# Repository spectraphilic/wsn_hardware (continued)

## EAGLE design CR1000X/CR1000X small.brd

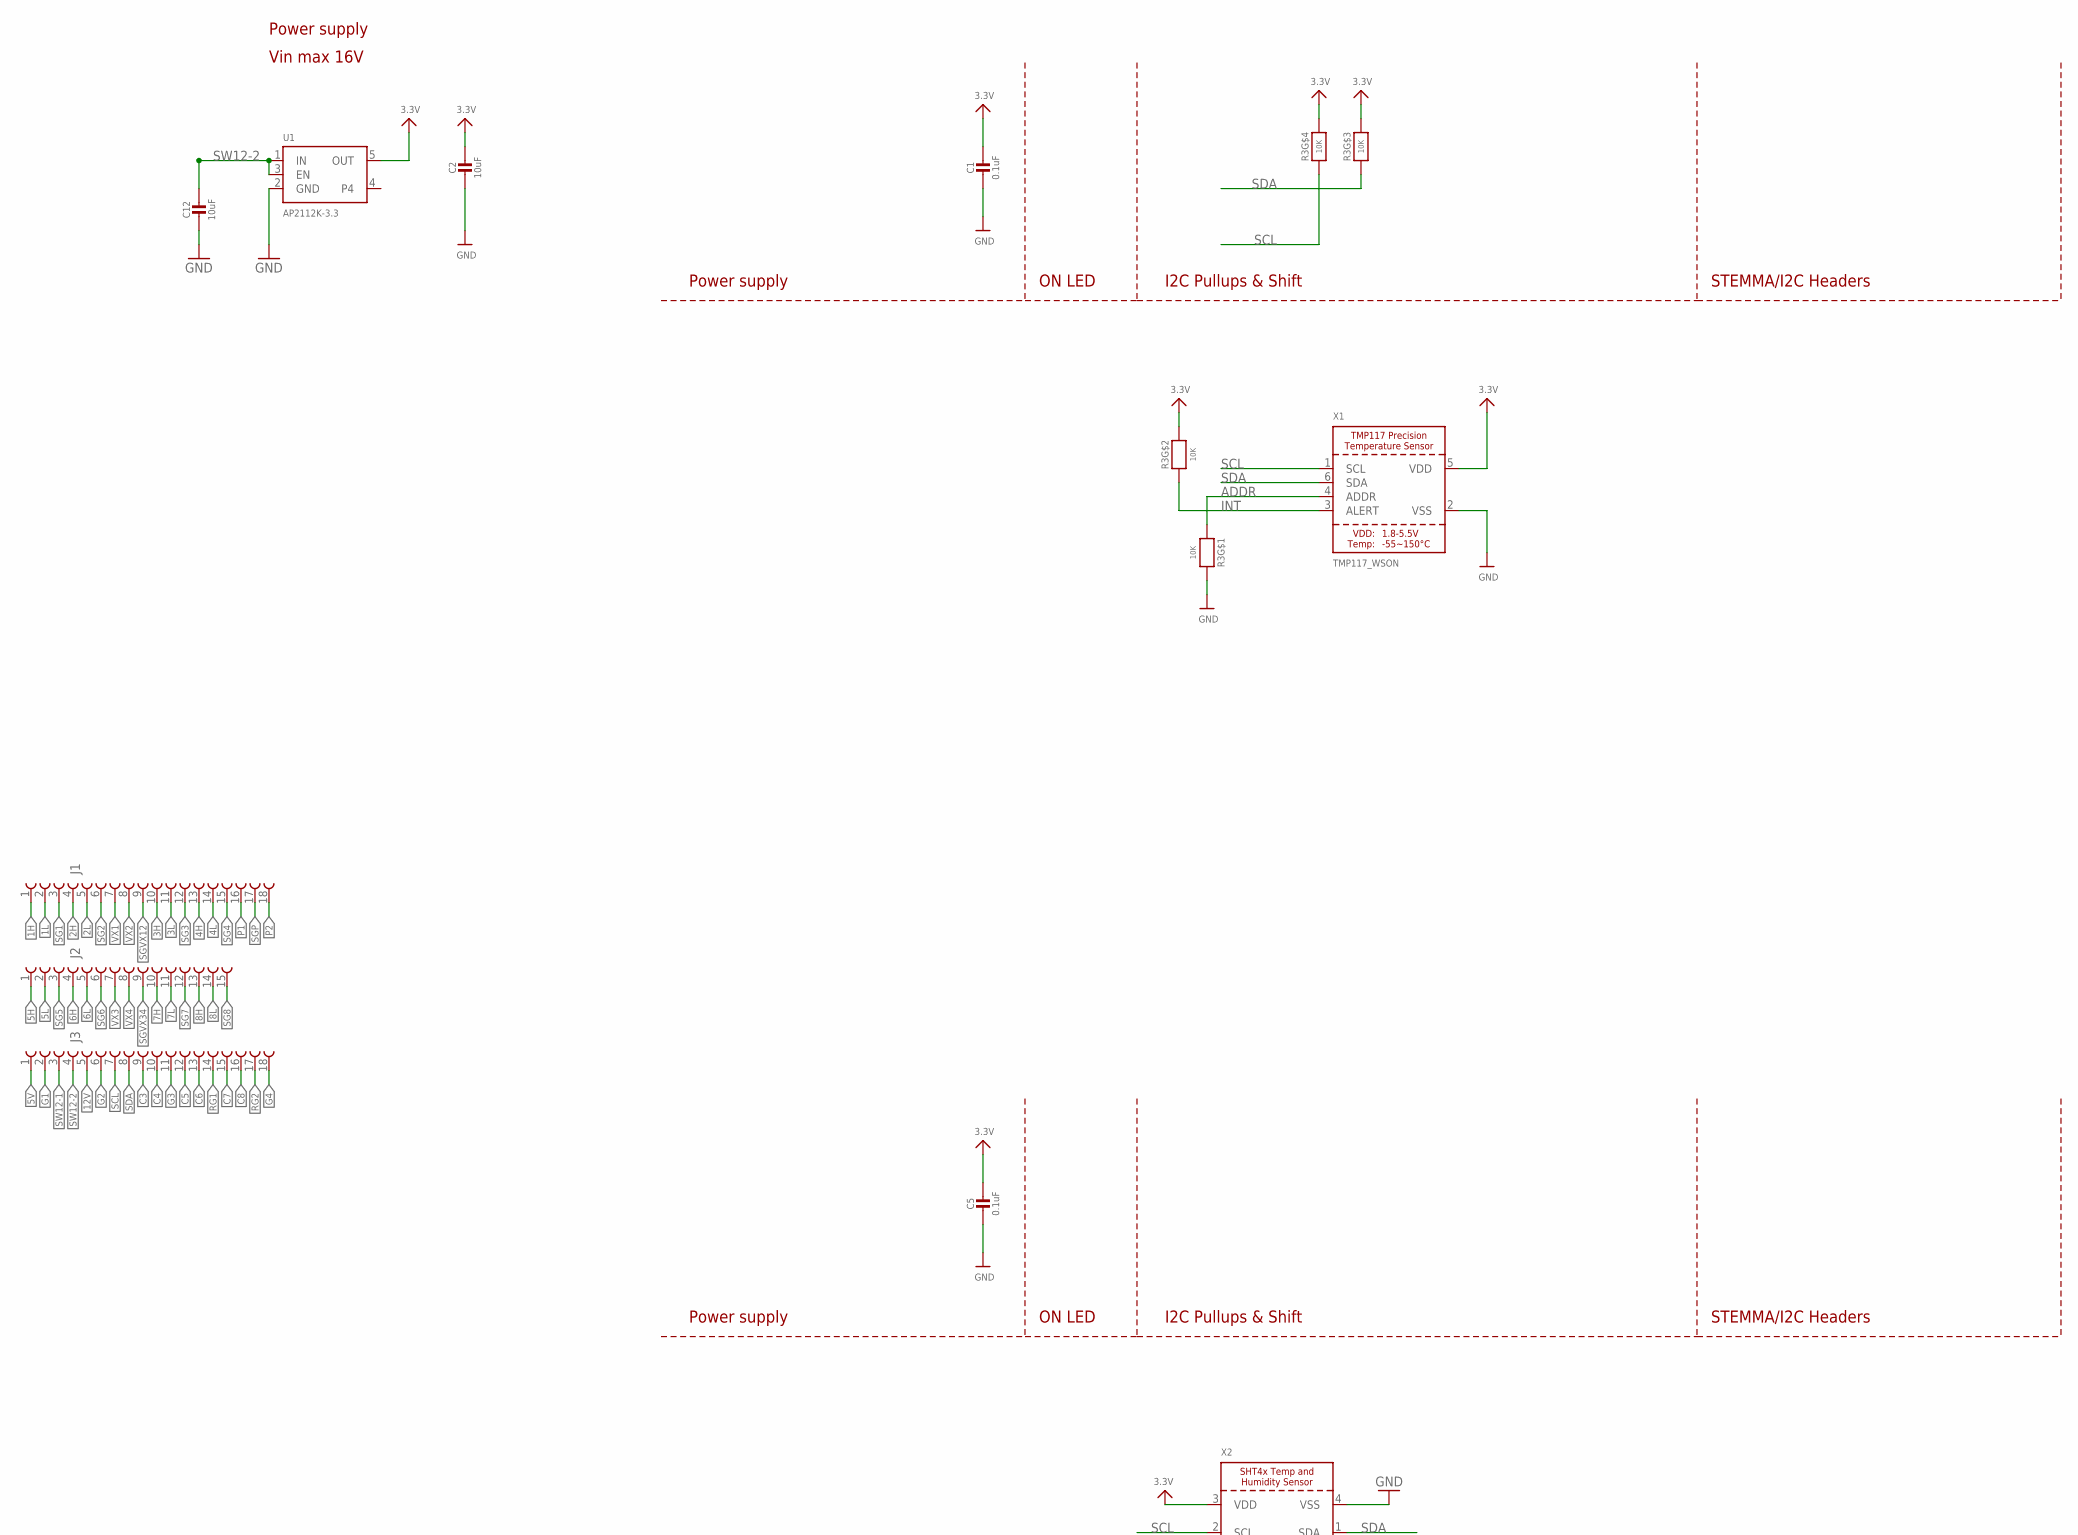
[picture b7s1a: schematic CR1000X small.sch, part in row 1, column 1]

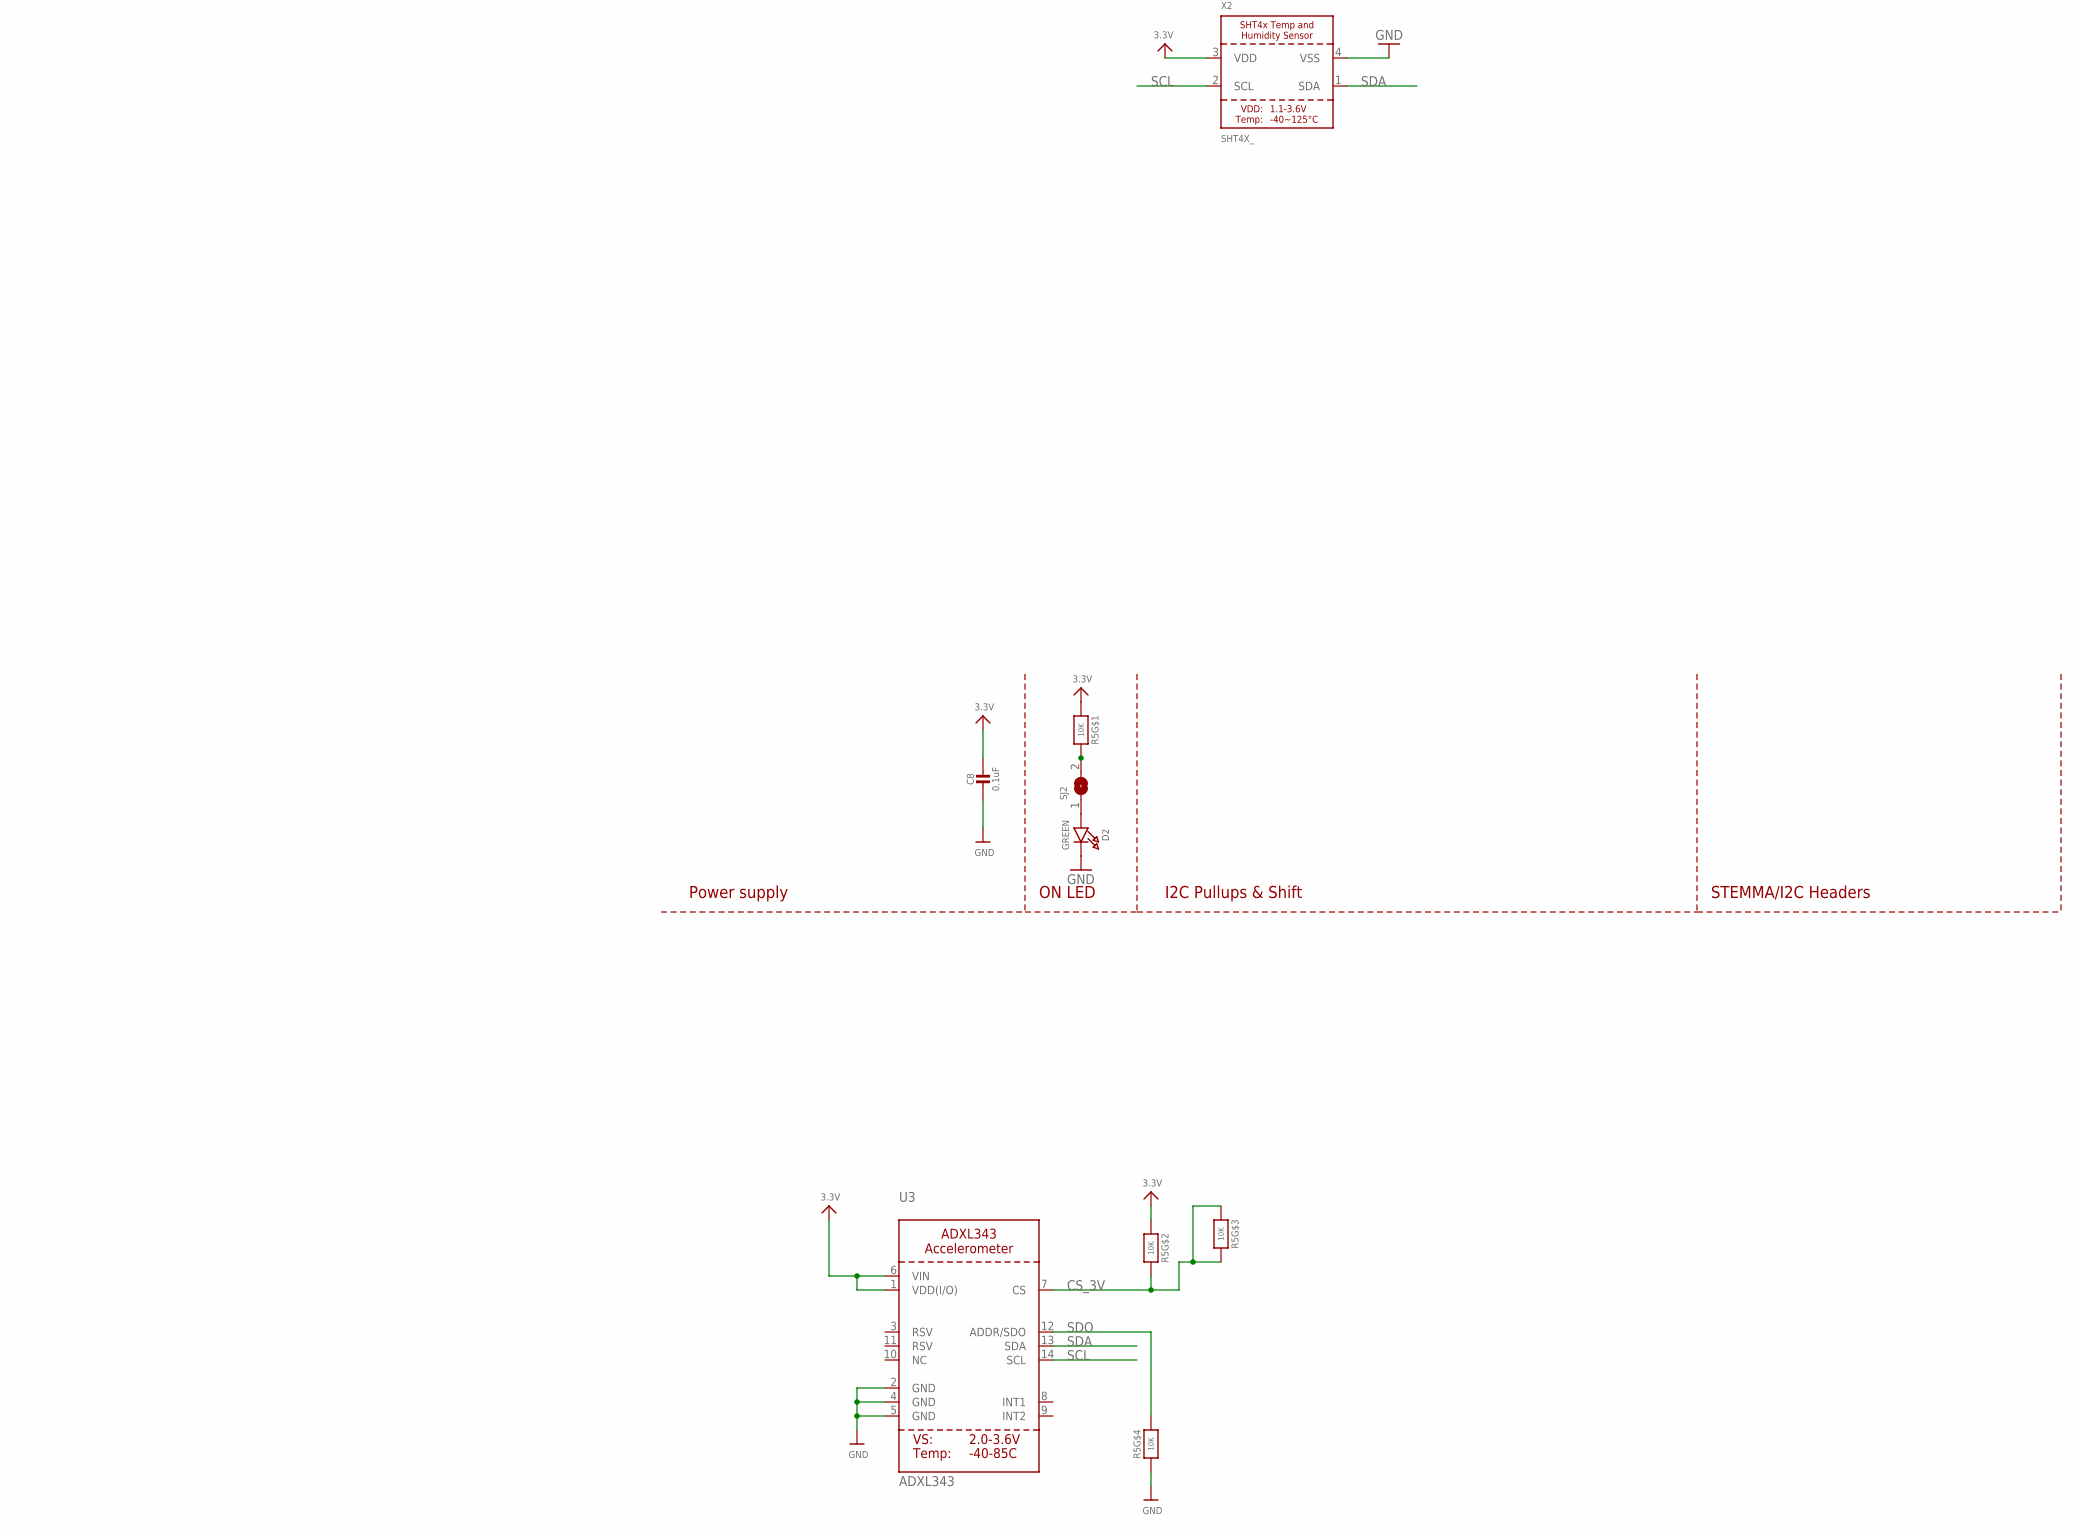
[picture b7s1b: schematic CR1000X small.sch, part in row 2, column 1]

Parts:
C1, C5, C8: 0.1uF; 0603-NO
C2, C12: 10uF; 0805-NO
D2: GREEN; CHIPLED_0603_NOOUTLINE
J1, J3: 691311500018
J2: 691311500015
R3, R5: 10K; RESPACK_4X0603
SJ2: SOLDERJUMPERCLOSED; SOLDERJUMPER_CLOSEDWIRE
U1: AP2112K-3.3; SOT23-5
U3: ADXL343; LGA14
X1: TMP117_WSON; WSON-6
X2: SHT4X_; SHT4X

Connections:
1H: J1.1
1L: J1.2
2H: J1.4
2L: J1.5
3.3V: C1.1, C2.1, C5.1, C8.1, R3.5 (2), R3.6 (2), R3.7 (2), R5.1, R5.2 (1), U1.5 (OUT), U3.1 (VDD(I/O)), U3.6 (VIN), X1.5 (VDD), X2.3 (VDD)
3H: J1.10
3L: J1.11
4H: J1.13
4L: J1.14
5H: J2.1
5L: J2.2
5V: J3.1
6H: J2.4
6L: J2.5
7H: J2.10
7L: J2.11
8H: J2.13
8L: J2.14
12V: J3.5
ADDR: R3.1, X1.4 (ADDR)
C3: J3.9
C4: J3.10
C5: J3.12
C6: J3.13
C7: J3.15
C8: J3.16
CS_3V: R5.3 (1), R5.6 (2), R5.7 (2), U3.7 (CS)
G1: J3.2
G2: J3.6
G3: J3.11
G4: J3.18
GND: C1.2, C2.2, C5.2, C8.2, C12.2, D2.C, R3.8 (2), R5.4 (1), U1.2 (GND), U3.2 (GND), U3.4 (GND), U3.5 (GND), X1.2 (VSS), X2.4 (VSS)
INT: R3.2 (1), X1.3 (ALERT)
unnamed: R5.8 (2), SJ2.2
unnamed: D2.A, SJ2.1
P1: J1.16
P2: J1.18
RG1: J3.14
RG2: J3.17
SCL: J3.7, R3.4 (1), U3.14 (SCL), X1.1 (SCL), X2.2 (SCL)
SDA: J3.8, R3.3 (1), U3.13 (SDA), X1.6 (SDA), X2.1 (SDA)
SDO: R5.5 (2), U3.12 (ADDR/SDO)
SG1: J1.3
SG2: J1.6
SG3: J1.12
SG4: J1.15
SG5: J2.3
SG6: J2.6
SG7: J2.12
SG8: J2.15
SGP: J1.17
SGVX12: J1.9
SGVX34: J2.9
SW12-1: J3.3
SW12-2: C12.1, J3.4, U1.1 (IN), U1.3 (EN)
VX1: J1.7
VX2: J1.8
VX3: J2.7
VX4: J2.8

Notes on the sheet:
I2C Pullups & Shift
STEMMA/I2C Headers
ON LED
Power supply
Vin max 16V

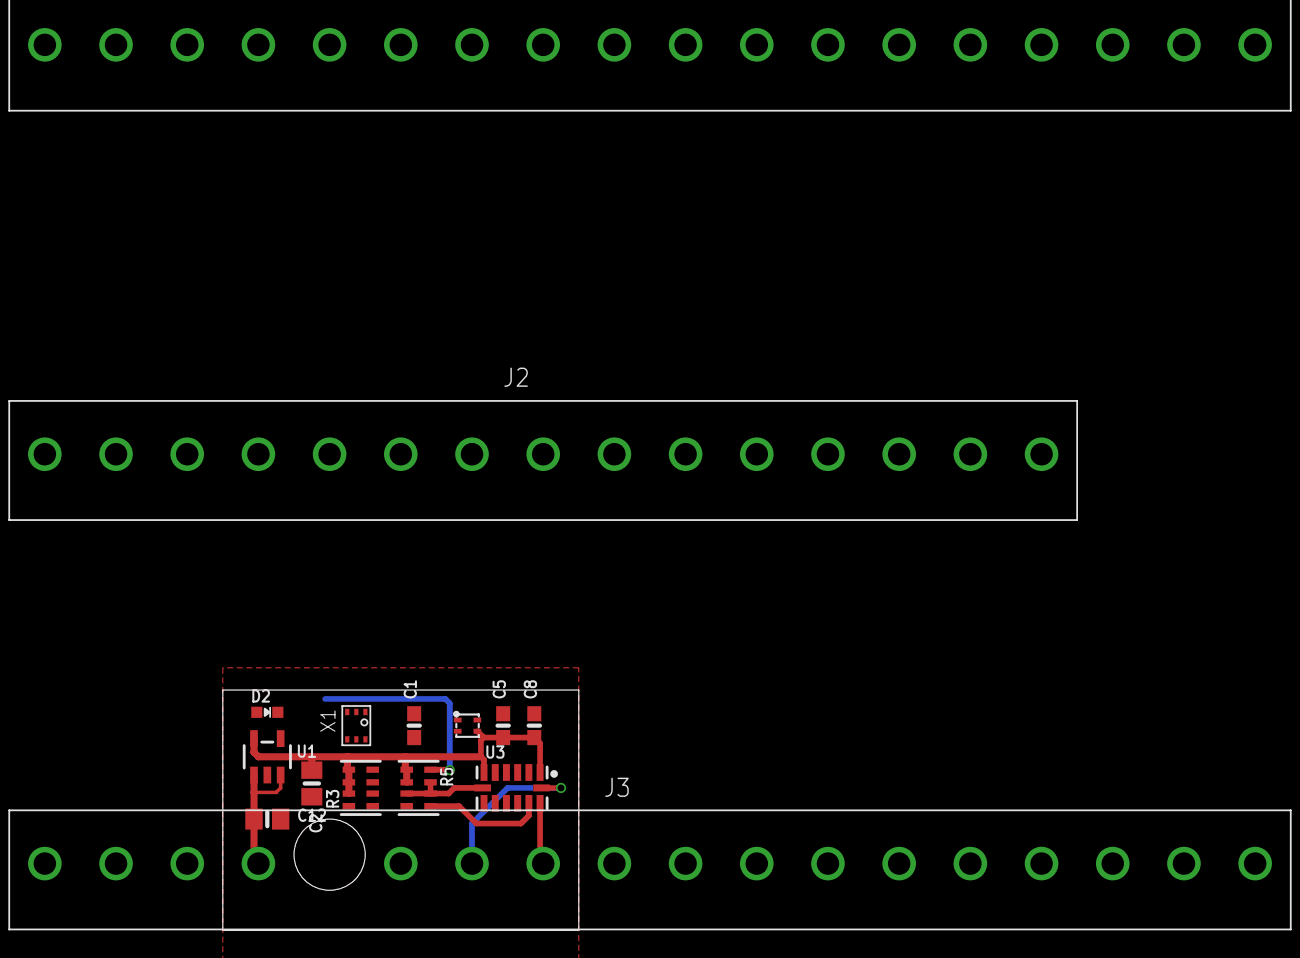
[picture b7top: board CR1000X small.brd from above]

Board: 2 copper layers, 25.4 x 17.1 mm, 16 parts (1 on the bottom side), 11 nets.

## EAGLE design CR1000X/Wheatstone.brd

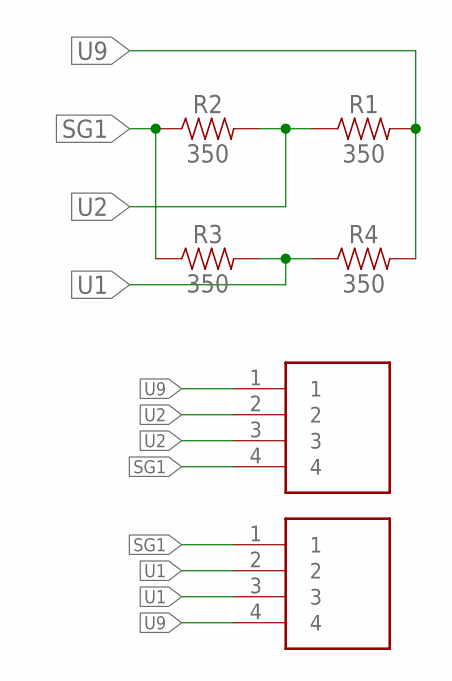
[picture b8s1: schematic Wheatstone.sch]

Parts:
J1, J2: 1725672; 1725672-4-2.54
R1, R2, R3, R4: 350; AXIAL-0.3

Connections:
SG1: J1.4, J2.1, R2.P$1 (1), R3.P$1 (1)
U1: J2.2, J2.3, R3.P$2 (2), R4.P$1 (1)
U2: J1.2, J1.3, R1.P$1 (1), R2.P$2 (2)
U9: J1.1, J2.4, R1.P$2 (2), R4.P$2 (2)

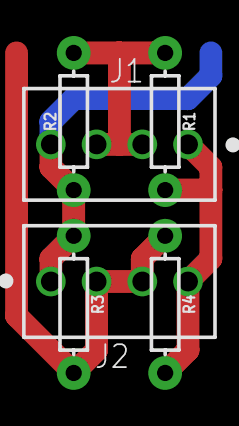
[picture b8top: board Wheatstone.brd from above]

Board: 2 copper layers, 6 parts (0 on the bottom side), 4 nets.

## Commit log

2018-09-26 Prototype of Lagopus boards
    Board A - round board
    Board B - temperature sond
2018-09-26 Seeed CAM job generator
2018-09-26 Temp_SMD Version 1
    This version was pruduced by SEEED
2018-09-26 Temp_THT
    Thru hole version of the temp board
2018-09-26 Johns library
2018-09-26 Produced Lemming sensor and power board
    This version was produced på Dirty PCB with THT components
2018-09-26 Added lemming THT
2018-09-26 organizing folders
2018-10-01 Change hole sizes and removed USB connector on the waspmote shield
2018-10-01 Lemming_SMD prototype
2018-10-23 Ordered Version 1.0 from Seeed
    Lemming_SMD V1.0
    Lagopus_A V1.0
    Lagopus_B V1.0
2018-10-29 Library from Seeed
2018-11-30 Backplate prototype ordered
2018-12-11 Changes suggested by SEEED
    Minor changes in Lagopus A and Backplate.
2018-12-14 Part list for WSN stations
2018-12-17 Linkes complete
2019-01-16 Ordered according to excel sheet
2019-01-25 Backplate v1.1 ordered
2019-01-28 Updated order status
2019-05-24 architecture diagram new system
2019-05-24 diagram correction
2019-06-05 added document about OSlogger design
2019-06-05 added diagram
2019-06-05 roadmap
2019-06-06 added nb-iot
2019-06-06 added nb-iot 2
2019-09-19 Lemming SMD v2.2
2019-11-27 Lagopus B 2.0
2019-11-27 Test Lagopus A 2.0
2019-11-29 Lagopus v2.0 Finished
2019-11-29 WSN v2 ready for review
2019-12-19 WSN 2 ready for quotations
2020-01-21 added OSlogger specs and ideas
2020-03-20 Order of v2
2020-08-31 DC-DC version1
2020-09-01 DC-DC version 2
2020-10-06 Lemming SMD new order 2020
2020-10-09 Minor changes befor order
2020-11-19 DCDC-Relay
2020-12-03 Wheatstone ordered
2020-12-11 John
2020-12-18 Merry Christmas
2020-12-21 Lagopus 3.0 order
2021-01-07 Started with backplate 2
2021-01-08 Lagopus 3 mm.
2021-01-08 Delete eagle.epf
    afdasdfsa
2021-01-08 Delete eagle.epf
    zczxcz
2021-01-08 adfasdfas
2021-01-11 kjafljah
2021-01-13 updated order list, TBC
2021-01-15 updated purchase list
2021-01-24 GNSS start
2021-06-13 Flamingo PCB
2021-06-14 Flamingo order
2021-06-15 Flamingo PCB radio
2021-06-15 Flamingo ordered from Eurocircuits
2022-03-16 Ploughmeter and others
2022-08-17 lemming v3 uploaded
2022-09-07 Added two more switches with external control
2022-10-06 CR1000X Boards
2025-01-06 mammamia3 etc
